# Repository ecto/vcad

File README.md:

# vcad

Open-source parametric CAD for the AI era.

**[Try it now →](https://vcad.io)**

## Features

- **Modeling** — Primitives, booleans, fillets, chamfers, shell
- **Sketching** — 2D constraints, extrude, revolve, sweep, loft
- **Assembly** — Parts, instances, joints, forward kinematics
- **Simulation** — Physics with phyz, gym-style RL interface
- **Import/Export** — STEP import, STL/GLB/STEP/DXF export
- **Rendering** — Direct BRep ray tracing + tessellated mode
- **Cloud** — Supabase sync with Google/GitHub auth

## Use vcad

### Web App

Visit [vcad.io](https://vcad.io) — no install required.

### Native Mac App

A native SwiftUI app lives in [`apple/VcadApp`](apple/VcadApp) (macOS only;
other platforms use the web app). Build it from source:

```bash
apple/VcadApp/build-ffi.sh   # build the vcad-ffi kernel static library
apple/VcadApp/bundle.sh      # assemble dist/vcad.app
open apple/VcadApp/dist/vcad.app
```

### CLI

```bash
cargo install vcad
vcad export input.vcad output.stl
vcad import-step input.step output.vcad
```

### MCP Server (AI Agents)

The MCP server lets AI agents create and manipulate CAD models:

```bash
npm install -g @vcad/mcp
```

Tools: `create_cad_document`, `export_cad`, `inspect_cad`, `gym_step`, `gym_reset`

### Rust Library

```rust
use vcad_kernel::Solid;

// Create a box with a hole
let solid = Solid::cube(100.0, 60.0, 20.0);
let hole = Solid::cylinder(10.0, 25.0, 32);
let result = solid - hole;

// Export to mesh
let mesh = result.to_mesh(32);
```

See [crates/vcad-kernel](crates/vcad-kernel) for the full API.

## Architecture

```
vcad/
├── crates/           # Rust BRep kernel (~35K LOC)
│   ├── vcad-kernel/  # Unified API
│   ├── vcad-kernel-topo/    # Half-edge topology
│   ├── vcad-kernel-booleans/# Boolean operations
│   └── ...           # 20+ modular crates
├── packages/         # TypeScript
│   ├── app/          # React + Three.js web app
│   ├── mcp/          # MCP server for AI agents
│   └── ...
└── supabase/         # Database migrations
```

## Development

> **Heads up:** vcad depends on the `tang` math workspace and the `phyz`
> physics workspace at **sibling paths** (`../tang`, `../phyz`). Clone both
> next to vcad before any `cargo` command, or the workspace will fail to
> resolve:
>
> ```bash
> git clone git@github.com:ecto/tang.git ../tang
> git clone git@github.com:ecto/phyz.git ../phyz
> ```

```bash
# Rust
cargo test --workspace
cargo clippy --workspace -- -D warnings

# TypeScript
npm ci
npm run dev -w @vcad/app   # Run web app locally

# Native Mac app (macOS + Xcode command-line tools)
apple/VcadApp/build-ffi.sh && apple/VcadApp/bundle.sh
```

## Export controls

The hosted services (vcad.io and mcp.vcad.io) are not available in
jurisdictions subject to U.S. sanctions and export controls — currently
Russia, Belarus, Iran, Cuba, North Korea, Syria, and the Crimea, Sevastopol,
Donetsk, and Luhansk regions of Ukraine. Users must comply with all
applicable export laws. The open-source code in this repository is not
affected and remains available to everyone. Details in
[docs/export-controls.md](docs/export-controls.md).

## License

Copyright © 2026 Municipal Robotics Corporation

Licensed under the [Apache License 2.0](LICENSE). See [NOTICE](NOTICE) for
attributions. Contributions are accepted under the same license per the
[Apache 2.0 Section 5](LICENSE) inbound-equals-outbound rule.

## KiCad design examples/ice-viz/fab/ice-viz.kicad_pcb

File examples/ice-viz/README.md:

# ice-viz — iCE40UP5K + RP2040 FPGA dev board

A pico-ice-style starter FPGA board designed entirely through the vcad MCP
tools: Lattice iCE40UP5K-SG48 with an RP2040 as on-board USB-C programmer
(shared SPI bus to the W25Q32 bitstream flash, CRESET/CDONE under RP2040
control — drag-and-drop UF2 programming, no external programmer), a 14-pin
header matching the common 2.8" ILI9341 SPI display breakout (+ XPT2046
touch), SWD header, and 8 spare FPGA IOs. 78×60 mm 2-layer, JLCPCB-compatible
rules, DRC-clean.

- `ice-viz.vcad` — the parametric source; reopen with the MCP `load_document`
  tool or vcad.io to edit and re-export.
- `fab/` — gerber/drill/BOM/pick-and-place bundle plus editable KiCad 9
  exports (`ice-viz.kicad_sch`, `ice-viz.kicad_pcb`).

Before ordering: verify the iCE40 SG48 and RP2040 pin maps against the
datasheets, and eyeball the parametric USB-C/QFN land patterns in KiCad.

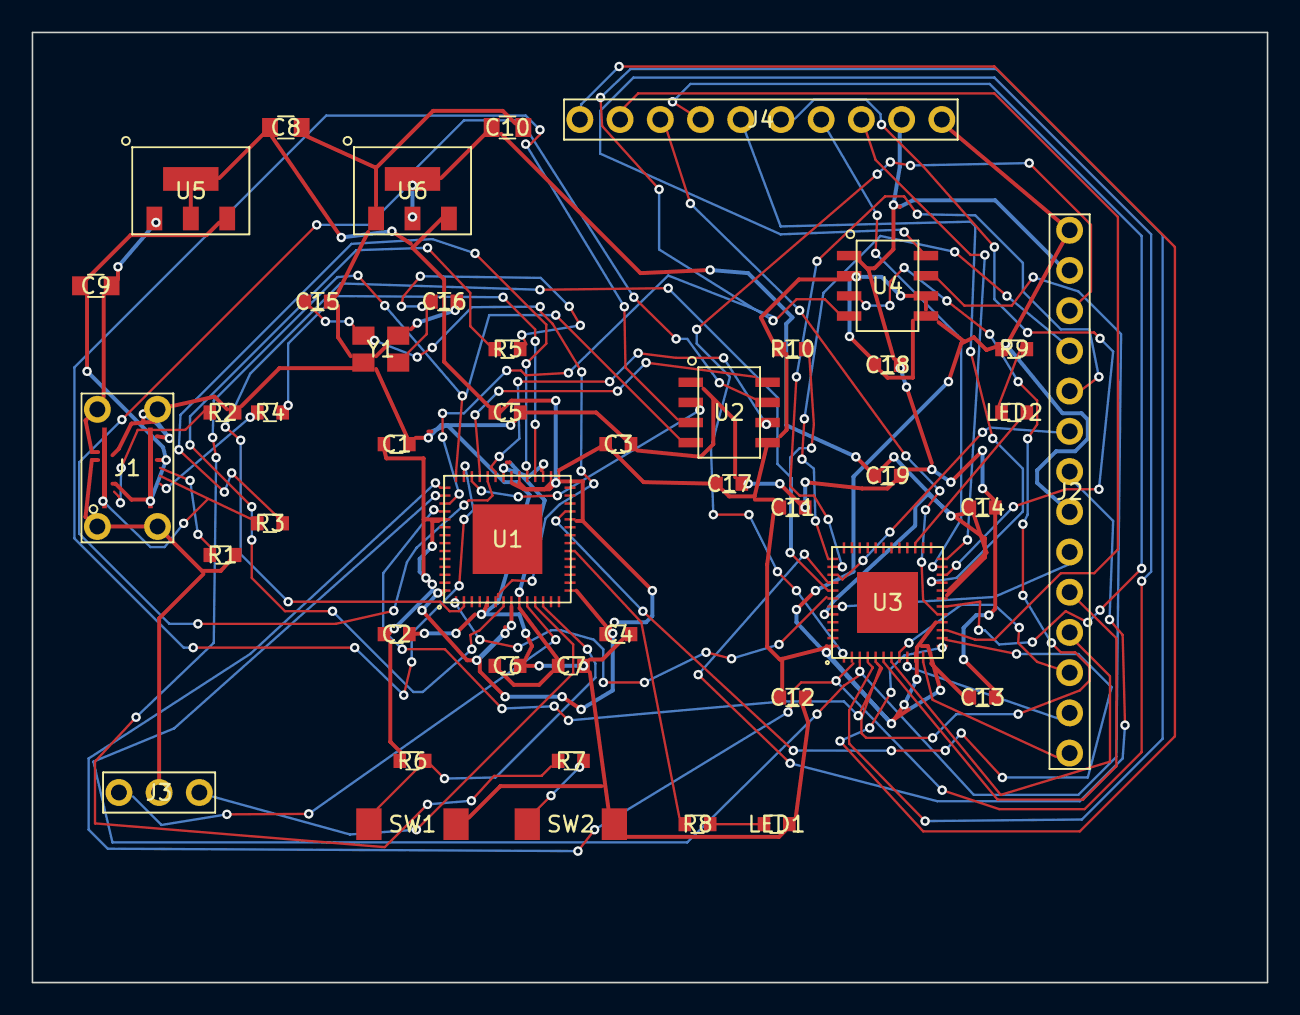
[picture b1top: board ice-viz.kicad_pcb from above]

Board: 2 copper layers, 78.0 x 60.0 mm, 44 parts (0 on the bottom side), 54 nets.

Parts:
C1, C2, C3, C4, C5, C6, C11, C12, C13, C14, C17, C18, C19: 100nF; C_0603
C7: 1uF; C_0603
C8, C9, C10: 10uF; C_0805
C15, C16: 27pF; C_0603
J1: USB-C-16P; USB-C
J2: ILI9341-LCD; PinHeader_1x14_P2.54mm
J3: SWD; PinHeader_1x03_P2.54mm
J4: FPGA-IO; PinHeader_1x10_P2.54mm
LED1: green; LED_0603
LED2: red; LED_0603
R1, R2: 5.1k; R_0603
R3, R4: 27; R_0603
R5, R7: 1k; R_0603
R6, R10: 10k; R_0603
R8, R9: 330; R_0603
SW1: RESET; SW_SMD_2P
SW2: BOOTSEL; SW_SMD_2P
U1: RP2040; QFN-56
U2: W25Q128JVS; SOIC-8
U3: iCE40UP5K-SG48I; QFN-48
U4: W25Q32JVSS; SOIC-8
U5: AMS1117-3.3; SOT-223
U6: AMS1117-1.2; SOT-223
Y1: 12MHz; Crystal_3225

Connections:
1V2: C10.1, C14.1, C19.1, U3.5, U3.29, U3.30, U6.2, U6.4
3V3: C1.1, C2.1, C3.1, C4.1, C5.1, C8.1, C11.1, C12.1, C13.1, C17.1, C18.1, J2.1, J2.8, J4.1, R6.1, R9.1, R10.1, U1.1, U1.10, U1.22, U1.33, U1.42, U1.43, U1.44, U1.48, U1.49, U2.8, U3.1, U3.22, U3.24, U3.33, U4.3, U4.7, U4.8, U5.2, U5.4, U6.3
BOOTSEL: R7.2, SW2.1
CC1: J1.5, R1.1
CC2: J1.17, R2.1
FIO1: J4.3, U3.25
FIO2: J4.4, U3.26
FIO3: J4.5, U3.27
FIO4: J4.6, U3.28
FIO5: J4.7, U3.31
FIO6: J4.8, U3.32
FIO7: J4.9, U3.34
FIO8: J4.10, U3.36
GND: C1.2, C2.2, C3.2, C4.2, C5.2, C6.2, C7.2, C8.2, C9.2, C10.2, C11.2, C12.2, C13.2, C14.2, C15.2, C16.2, C17.2, C18.2, C19.2, J1.1, J1.12, J1.13, J1.SH1, J1.SH2, J1.SH3, J1.SH4, J2.2, J3.2, J4.2, LED1.2, R1.2, R2.2, SW1.2, SW2.2, U1.19, U2.4, U4.4, U5.1, U6.1, Y1.2, Y1.4
ICE_CDONE: U1.15, U3.7
ICE_CRESET: R10.2, U1.16, U3.8
ICE_MISO: U1.11, U3.17, U4.2
ICE_MOSI: U1.14, U3.14, U4.5
ICE_SCK: U1.13, U3.15, U4.6
ICE_SS: U1.12, U3.16, U4.1
LCD_CS: J2.3, U3.13
LCD_DC: J2.5, U3.11
LCD_MISO: J2.9, U3.6
LCD_MOSI: J2.6, U3.10
LCD_RST: J2.4, U3.12
LCD_SCK: J2.7, U3.9
LED2_A: LED2.1, R9.2
LED2_K: LED2.2, U3.39
QSPI_SCLK: U1.52, U2.6
QSPI_SD0: U1.53, U2.5
QSPI_SD1: U1.55, U2.2
QSPI_SD2: U1.54, U2.3
QSPI_SD3: U1.51, U2.7
QSPI_SS: R7.1, U1.56, U2.1
RP_CLK: U1.32, U3.35
RP_DVDD: C6.1, C7.1, U1.23, U1.45, U1.50
RP_LED: R8.1, U1.37
RP_LED_A: LED1.1, R8.2
RUN: R6.2, SW1.1, U1.26
SWCLK: J3.3, U1.24
SWDIO: J3.1, U1.25
T_CLK: J2.10, U3.18
T_CS: J2.11, U3.19
T_DIN: J2.12, U3.20
T_DO: J2.13, U3.21
T_IRQ: J2.14, U3.23
USB_DN: R4.2, U1.46
USB_DN_J: J1.7, R4.1
USB_DP: R3.2, U1.47
USB_DP_J: J1.6, J1.18, R3.1
VBUS: C9.1, J1.4, J1.9, J1.16, U5.3
XIN: C15.1, U1.20, Y1.1
XOUT: C16.1, R5.2, Y1.3
XOUT_R: R5.1, U1.21
